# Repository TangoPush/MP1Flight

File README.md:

# MP1Flight

STM32MP1 based flight controller based off the Pixracer.

Slack channel available here:

https://join.slack.com/t/mp1flight/shared_invite/zt-ewtdxsr4-UjyOhen2aBG~TFt4L_m_wA

Current status:

Still working through developing the first PCB, please contribute at this stage with any features or changes.

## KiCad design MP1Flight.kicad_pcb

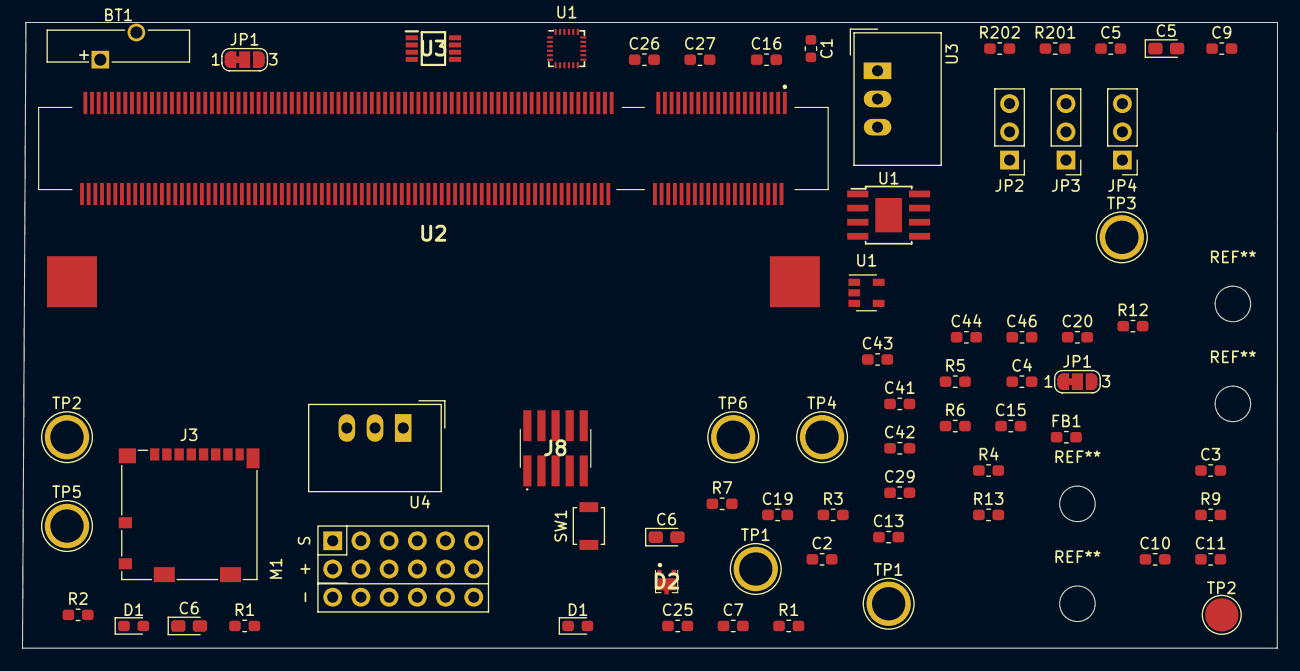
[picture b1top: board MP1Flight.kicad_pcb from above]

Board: 2 copper layers, 113.0 x 56.3 mm, 68 parts (0 on the bottom side), 53 nets, no tracks yet.

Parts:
BT1: Battery_Cell; Battery_Panasonic_CR1220-VCN_Vertical_CircularHoles
C1: 100nF; C_0603_1608Metric
C2, C3, C4, C5, C7, C9, C10, C11, C13, C15, C16, C19, C20, C27, C29, C41, C42, C43, C44, C46: 100nF; C_0603_1608Metric_Pad1.05x0.95mm_HandSolder
C5#2: 1uF; CP_EIA-2012-15_AVX-P_Pad1.30x1.05mm_HandSolder
C6: 100uF; CP_EIA-2012-15_AVX-P_Pad1.30x1.05mm_HandSolder
C6#2: 0.1uF; CP_EIA-2012-15_AVX-P_Pad1.30x1.05mm_HandSolder
C25, C26: 10uF; C_0603_1608Metric_Pad1.05x0.95mm_HandSolder
D1, D1#2: LED; LED_0603_1608Metric_Pad1.05x0.95mm_HandSolder
D2: PMEG2020CPA,115; PMEG2020CPA115
FB1: Ferrite_Bead; L_0603_1608Metric_Pad1.05x0.95mm_HandSolder
J3: Micro_SD_Card_Det; microSD_HC_Molex_104031-0811
J8: Conn_ARM_JTAG_SWD_10; FTSH10501LDVKPTR
JP1, JP1#2: SolderJumper_3_Bridged12; SolderJumper-3_P1.3mm_Bridged12_RoundedPad1.0x1.5mm_NumberL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
JP2, JP3, JP4: Jumper_3_Bridged12; PinHeader_1x03_P2.54mm_Vertical
M1: Servo_Connector; 3_6_2_54mm
R1, R1#2: 330; R_0603_1608Metric_Pad1.05x0.95mm_HandSolder
R2, R5: 1M; R_0603_1608Metric_Pad1.05x0.95mm_HandSolder
R3, R4: DNF; R_0603_1608Metric_Pad1.05x0.95mm_HandSolder
R6, R7: 10k; R_0603_1608Metric_Pad1.05x0.95mm_HandSolder
R9: 12k; R_0603_1608Metric_Pad1.05x0.95mm_HandSolder
R12: 1K5; R_0603_1608Metric_Pad1.05x0.95mm_HandSolder
R13: 2k2; C_0603_1608Metric_Pad1.05x0.95mm_HandSolder
R201: 2k2; R_0603_1608Metric_Pad1.05x0.95mm_HandSolder
R202: 2K2; R_0603_1608Metric_Pad1.05x0.95mm_HandSolder
SW1: SW_Push; SW_SPST_B3U-1000P
TP1, TP1#2, TP2, TP3, TP4, TP5, TP6: TestPoint; TestPoint_Plated_Hole_D3.0mm
TP2#2: TestPoint; TestPoint_Pad_D3.0mm
U1: TPS79318-EP; SOT-23-5
U1#2: MPU-9250; InvenSense_QFN-24_3x3mm_P0.4mm
U1#3: ST1S10PHR; TI_SO-PowerPAD-8
U2: VisionSOM-STM32MP1; 17172544
U3: 74LVC2G86; SOP65P400X130-8N
U3#2: TSR_1-2450; Converter_DCDC_TRACO_TSR-1_THT
U4: TSR_1-2433; Converter_DCDC_TRACO_TSR-1_THT

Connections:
+3V3: C5.1, C10.1, C11.1, C16.1, C26.1, C27.1, JP1.3, R201.1, R202.1, U1#2.1, U1#2.8, U1#2.13, U3.8, U4.3
+5V: C6.1, C6#2.1, C7.1, C25.1, D2.3, D2.4, R1.1, R1#2.1, TP1.1, TP1#2.1, U2.96, U2.98, U2.100, U2.102, U2.104, U2.106, U2.108, U2.110, U2.112, U3#2.3, U4.1
/ABAT: R3.1, R7.2, U2.157
/BATT_CURRENT_SENS: C19.1, R2.1, R7.1
/BATT_VOLT_SENS: C15.1, R5.1, R6.1
/BOOT0: JP2.2, U2.9
/BOOT1: JP3.2, U2.7
/BOOT2: JP4.2, U2.10
/FRSKY_INV: U2.113, U3.2, U3.5
/I2C1_SCL: R202.2, U2.151
/I2C1_SDA: R201.2, U2.49
/MISO: TP4.1, U1#2.9, U2.119
/MOSI: TP3.1, U1#2.24, U2.47
/MPU9250_CS: U1#2.22, U2.55
/MPU9250_DRDY: TP6.1, U1#2.12, U2.58
/PWM1: M1.1, U2.138
/PWM2: M1.4, U2.149
/PWM3: M1.7, U2.140
/PWM4: M1.10, U2.150
/PWM5: M1.13, U2.131
/PWM6: M1.16, U2.148
/SCLK: TP5.1, U2.129
/SD2-CLK: J3.5, U2.179
/SD2-CMD: J3.3, U2.173
/SD2-DATA0: J3.7, U2.167
/SD2-DATA1: J3.8, U2.171
/SD2-DATA2: J3.1, U2.175
/SD2-DATA3: J3.2, U2.169
/SDCard/Filtered_VDD: FB1.2, J3.4
/SDCard/VDD_SDCARD: C20.1, FB1.1
/STM32-NRST: J8.10, SW1.2, U2.4, U2.48
/SWDCLK: J8.4, U2.54
/SWDIO: J8.2, U2.46
/SWO: J8.6, U2.52
/Safety_Switch_In: R12.2, U2.117
/Sensors_PowerDomain1/IMU_VDD_1V8: C44.1, C46.1, U1.5
/Sensors_PowerDomain1/VDD_3V3_Sensors: C29.1, C41.1, C42.1, C43.1, U1.1
/TDI: J8.8, U2.43
/USART6-RXD: U2.68, U3.7
/USART6-TXD: U2.79, U3.6
/VBAT: R4.1, R6.2, U2.62
/VIN: C5#2.1, U3#2.1
GND: BT1.2, C1.2, C2.2, C3.2, C4.2, C5.2, C5#2.2, C6.2, C6#2.2, C7.2, C9.2, C10.2, C11.2, C13.2, C15.2, C16.2, C19.2, C20.2, C25.2, C26.2, C27.2, C29.2, C41.2, C42.2, C43.2, C44.2, C46.2, D1.1, D1#2.1, J3.6, J3.11, J8.3, J8.5, J8.9, JP2.3, JP3.3, JP4.3, M1.3, M1.6, M1.9, M1.12, M1.15, M1.18, R2.2, R3.2, R4.2, R5.2, R9.2, R12.1, R13.2, SW1.1, TP2#2.1, U1#2.11, U1#2.18, U1#2.20, U2.1, U2.2, U2.15, U2.17, U2.20, U2.22, U2.23, U2.26, U2.28, U2.29, U2.35, U2.38, U2.40, U2.41, U2.50, U2.51, U2.59, U2.60, U2.70, U2.71, U2.81, U2.82, U2.84, U2.103, U2.107, U2.115, U2.116, U2.120, U2.125, U2.127, U2.128, U2.130, U2.132, U2.133, U2.135, U2.136, U2.143, U2.144, U2.145, U2.146, U2.147, U2.153, U2.155, U2.156, U2.159, U2.165, U2.168, U2.170, U2.172, U2.174, U2.176, U2.177, U2.178, U2.180, U2.181, U2.182, U2.184, U2.185, U2.189, U2.199, U2.200, U3.4, U3#2.2, U4.2
unnamed: BT1.1, C2.1, U2.8
unnamed: C4.1, JP1#2.2
unnamed: C9.1, TP2.1, U1#2.10
unnamed: C13.1, J8.1, JP1.2
unnamed: D1.2, D1#2.2, R1.2, R1#2.2
unnamed: U2.85, U2.87, U2.88, U2.89, U2.90, U2.91, U2.92, U2.93
unnamed: M1.2, M1.5, M1.8, M1.11, M1.14, M1.17
unnamed: U1.2, U1#3.2
unnamed: U1#2.7, U1#3.7
VDD: C1.1, JP1.1, JP2.1, JP3.1, JP4.1, U2.6

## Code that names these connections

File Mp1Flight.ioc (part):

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Mcu.Name=STM32MP157AABx
Mcu.Package=LFBGA354
Mcu.UserName=STM32MP157AABx
PA0.GPIOParameters=GPIO_Label
PA0.GPIO_Label=VBAT
PA0.Mode=IN16-Differential
PA0.Signal=ADC1_INP16
PA1.GPIOParameters=GPIO_Label
PA1.GPIO_Label=ABAT
PA1.Mode=IN16-Differential
PA1.Signal=ADC1_INN16
PA10.Mode=Asynchronous
PA10.Signal=USART1_RX
PA11.Mode=CTS_RTS
PA11.Signal=USART1_CTS
PA12.Mode=CTS_RTS
PA12.Signal=USART1_RTS
PA13.ContextOwner=CortexA7NS
PA13.GPIOParameters=GPIO_Label
PA13.GPIO_Label=FRSKY_INV
PA13.Signal=GPIO_Output
PA14.GPIOParameters=GPIO_Label
PA14.GPIO_Label=Safety_Switch_In
PA14.Signal=GPIO_Input
PA15.Signal=SDMMC1_D5
PA2.GPIOParameters=GPIO_PuPd
PA2.GPIO_PuPd=GPIO_PULLUP
PA2.Mode=RMII (Reduced MII)
PA2.Signal=ETH1_MDIO
PA3.GPIOParameters=GPIO_Label
PA3.GPIO_Label=PWM2
PA3.Signal=S_TIM2_CH4
PA5.GPIOParameters=GPIO_Label
PA5.GPIO_Label=PWM3
PA5.Signal=S_TIM2_CH1
PA7.Mode=RMII (Reduced MII)
PA7.Signal=ETH1_CRS_DV
PA8.GPIOParameters=GPIO_Label
PA8.GPIO_Label=PWM5
PA8.Signal=S_TIM1_CH1
PA9.Mode=Full_Duplex_Master
PA9.Signal=SPI2_SCK
PB0.GPIOParameters=GPIO_Label
PB0.GPIO_Label=PWM1
PB0.Signal=S_TIM3_CH3
PB1.Signal=ADCx_INP5
PB10.GPIOParameters=GPIO_Label
PB10.GPIO_Label=PWM4
PB10.Signal=S_TIM2_CH3
PB11.Mode=RMII (Reduced MII)
PB11.Signal=ETH1_TX_EN
PB13.Mode=RMII (Reduced MII)
PB13.Signal=ETH1_TXD1
PB14.Mode=SD_4_bits_Wide_bus
PB14.Signal=SDMMC2_D0
PB15.Mode=SD_4_bits_Wide_bus
PB15.Signal=SDMMC2_D1
PB2.Mode=Asynchronous
PB2.Signal=UART4_RX
PB3.Mode=SD_4_bits_Wide_bus
PB3.Signal=SDMMC2_D2
PB4.Mode=SD_4_bits_Wide_bus
PB4.Signal=SDMMC2_D3
PB5.Mode=ETH Clock Output (PHY without Quartz)
PB5.Signal=ETH1_CLK
PB6.Mode=Asynchronous
PB6.Signal=USART1_TX
PB7.GPIOParameters=GPIO_Label
PB7.GPIO_Label=Safety_LED
PB7.Signal=GPIO_Output
PB8.Mode=I2C
PB8.Signal=I2C1_SCL
PB9.Signal=LTDC_B7
PC0.ContextOwner=CortexA7NS
PC0.GPIOParameters=GPIO_Label
PC0.GPIO_Label=MPU9250_CS
PC0.Signal=GPIO_Output
PC1.GPIOParameters=GPIO_PuPd
PC1.GPIO_PuPd=GPIO_PULLUP
PC1.Mode=RMII (Reduced MII)
PC1.Signal=ETH1_MDC
PC11.Mode=SD_4_bits_Wide_bus
PC11.Signal=SDMMC1_D3
PC12.Mode=SD_4_bits_Wide_bus
PC12.Signal=SDMMC1_CK
PC13.Mode=RTC_OUT2_RMP
PC13.Signal=RTC_LSCO
PC14-OSC32_IN.Mode=LSE-External-Oscillator
PC14-OSC32_IN.Signal=RCC_OSC32_IN
PC15-OSC32_OUT.Mode=LSE-External-Oscillator
PC15-OSC32_OUT.Signal=RCC_OSC32_OUT
PC2.Mode=Full_Duplex_Master
PC2.Signal=SPI2_MISO
PC3.Mode=Full_Duplex_Master
PC3.Signal=SPI2_MOSI
PC4.Mode=RMII (Reduced MII)
PC4.Signal=ETH1_RXD0
PC5.Mode=RMII (Reduced MII)
PC5.Signal=ETH1_RXD1
PC8.Mode=SD_4_bits_Wide_bus
PC8.Signal=SDMMC1_D0
PC9.Mode=SD_4_bits_Wide_bus
PC9.Signal=SDMMC1_D1
PD0.Mode=SD_4_bits_Wide_bus
PD0.Signal=SDMMC3_CMD
PD1.Mode=SD_4_bits_Wide_bus
PD1.Signal=SDMMC3_D0
PD11.Mode=CTS_RTS
PD11.Signal=USART3_CTS
PD12.Mode=CTS_RTS
PD12.Signal=USART3_RTS
PD13.Mode=I2C
PD13.Signal=I2C1_SDA
PD14.Mode=CTS_RTS
PD14.Signal=UART8_CTS
PD15.Signal=S_TIM4_CH4
PD2.Mode=SD_4_bits_Wide_bus
PD2.Signal=SDMMC1_CMD
PD3.Signal=SDMMC1_D7
PD4.Mode=SD_4_bits_Wide_bus
PD4.Signal=SDMMC3_D1
PD5.Mode=SD_4_bits_Wide_bus
PD5.Signal=SDMMC3_D2
PD7.Mode=SD_4_bits_Wide_bus
PD7.Signal=SDMMC3_D3
PD8.Mode=Asynchronous
PD8.Signal=USART3_TX
PD9.Mode=Asynchronous
PD9.Signal=USART3_RX
PE0.Mode=Asynchronous
PE0.Signal=UART8_RX
PE1.Mode=Asynchronous
PE1.Signal=UART8_TX
PE10.Mode=CTS_RTS
PE10.Signal=UART7_CTS
PE11.GPIOParameters=GPIO_Label
PE11.GPIO_Label=PWM6
PE11.Signal=S_TIM1_CH2
PE14.Signal=LTDC_CLK
PE3.Mode=SD_4_bits_Wide_bus
PE3.Signal=SDMMC2_CK
PE4.Signal=SDMMC1_D4
PE5.Signal=SDMMC1_D6
PE6.Mode=SD_4_bits_Wide_bus
PE6.Signal=SDMMC1_D2
PE7.Mode=Asynchronous
PE7.Signal=UART7_RX
PE8.Mode=Asynchronous
PE8.Signal=UART7_TX
PF8.Mode=CTS_RTS
PF8.Signal=UART7_RTS
PG11.Mode=Asynchronous
PG11.Signal=UART4_TX
PG13.Mode=RMII (Reduced MII)
PG13.Signal=ETH1_TXD0
PG14.Mode=Asynchronous
PG14.Signal=USART6_TX
PG15.Mode=SD_4_bits_Wide_bus
PG15.Signal=SDMMC3_CK
PG6.Mode=SD_4_bits_Wide_bus
PG6.Signal=SDMMC2_CMD
PG7.Mode=CTS_RTS
PG7.Signal=UART8_RTS
PG8.Signal=LTDC_G7
PG9.Mode=Asynchronous
PG9.Signal=USART6_RX
PH0-OSC_IN.Mode=HSE-External-Clock-Source
PH0-OSC_IN.Signal=RCC_OSC_IN
RCC.HSE_VALUE=24000000
board=custom

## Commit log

2020-05-25 Initial commit: Completed significant portion of the schematic
2020-05-25 adding in SD card with power switch
2020-05-26 Moved connectors to child sheet
2020-05-26 Updated sheet titles
2020-05-26 Added in Debug sheet
2020-05-26 Added in SD Card Sheet plus made SD card connections
2020-05-26 Added in Servo Outputs and Setup the timers in CubeMX
2020-05-27 Added in Buzzer and N channel mosfet
2020-05-27 Safety LED, Alarm and Safety switch additions
2020-05-28 IMU1/2 added in plus regs
2020-05-30 Added in Magnetometer and barometer
2020-05-30 Wired up IMUs signals
